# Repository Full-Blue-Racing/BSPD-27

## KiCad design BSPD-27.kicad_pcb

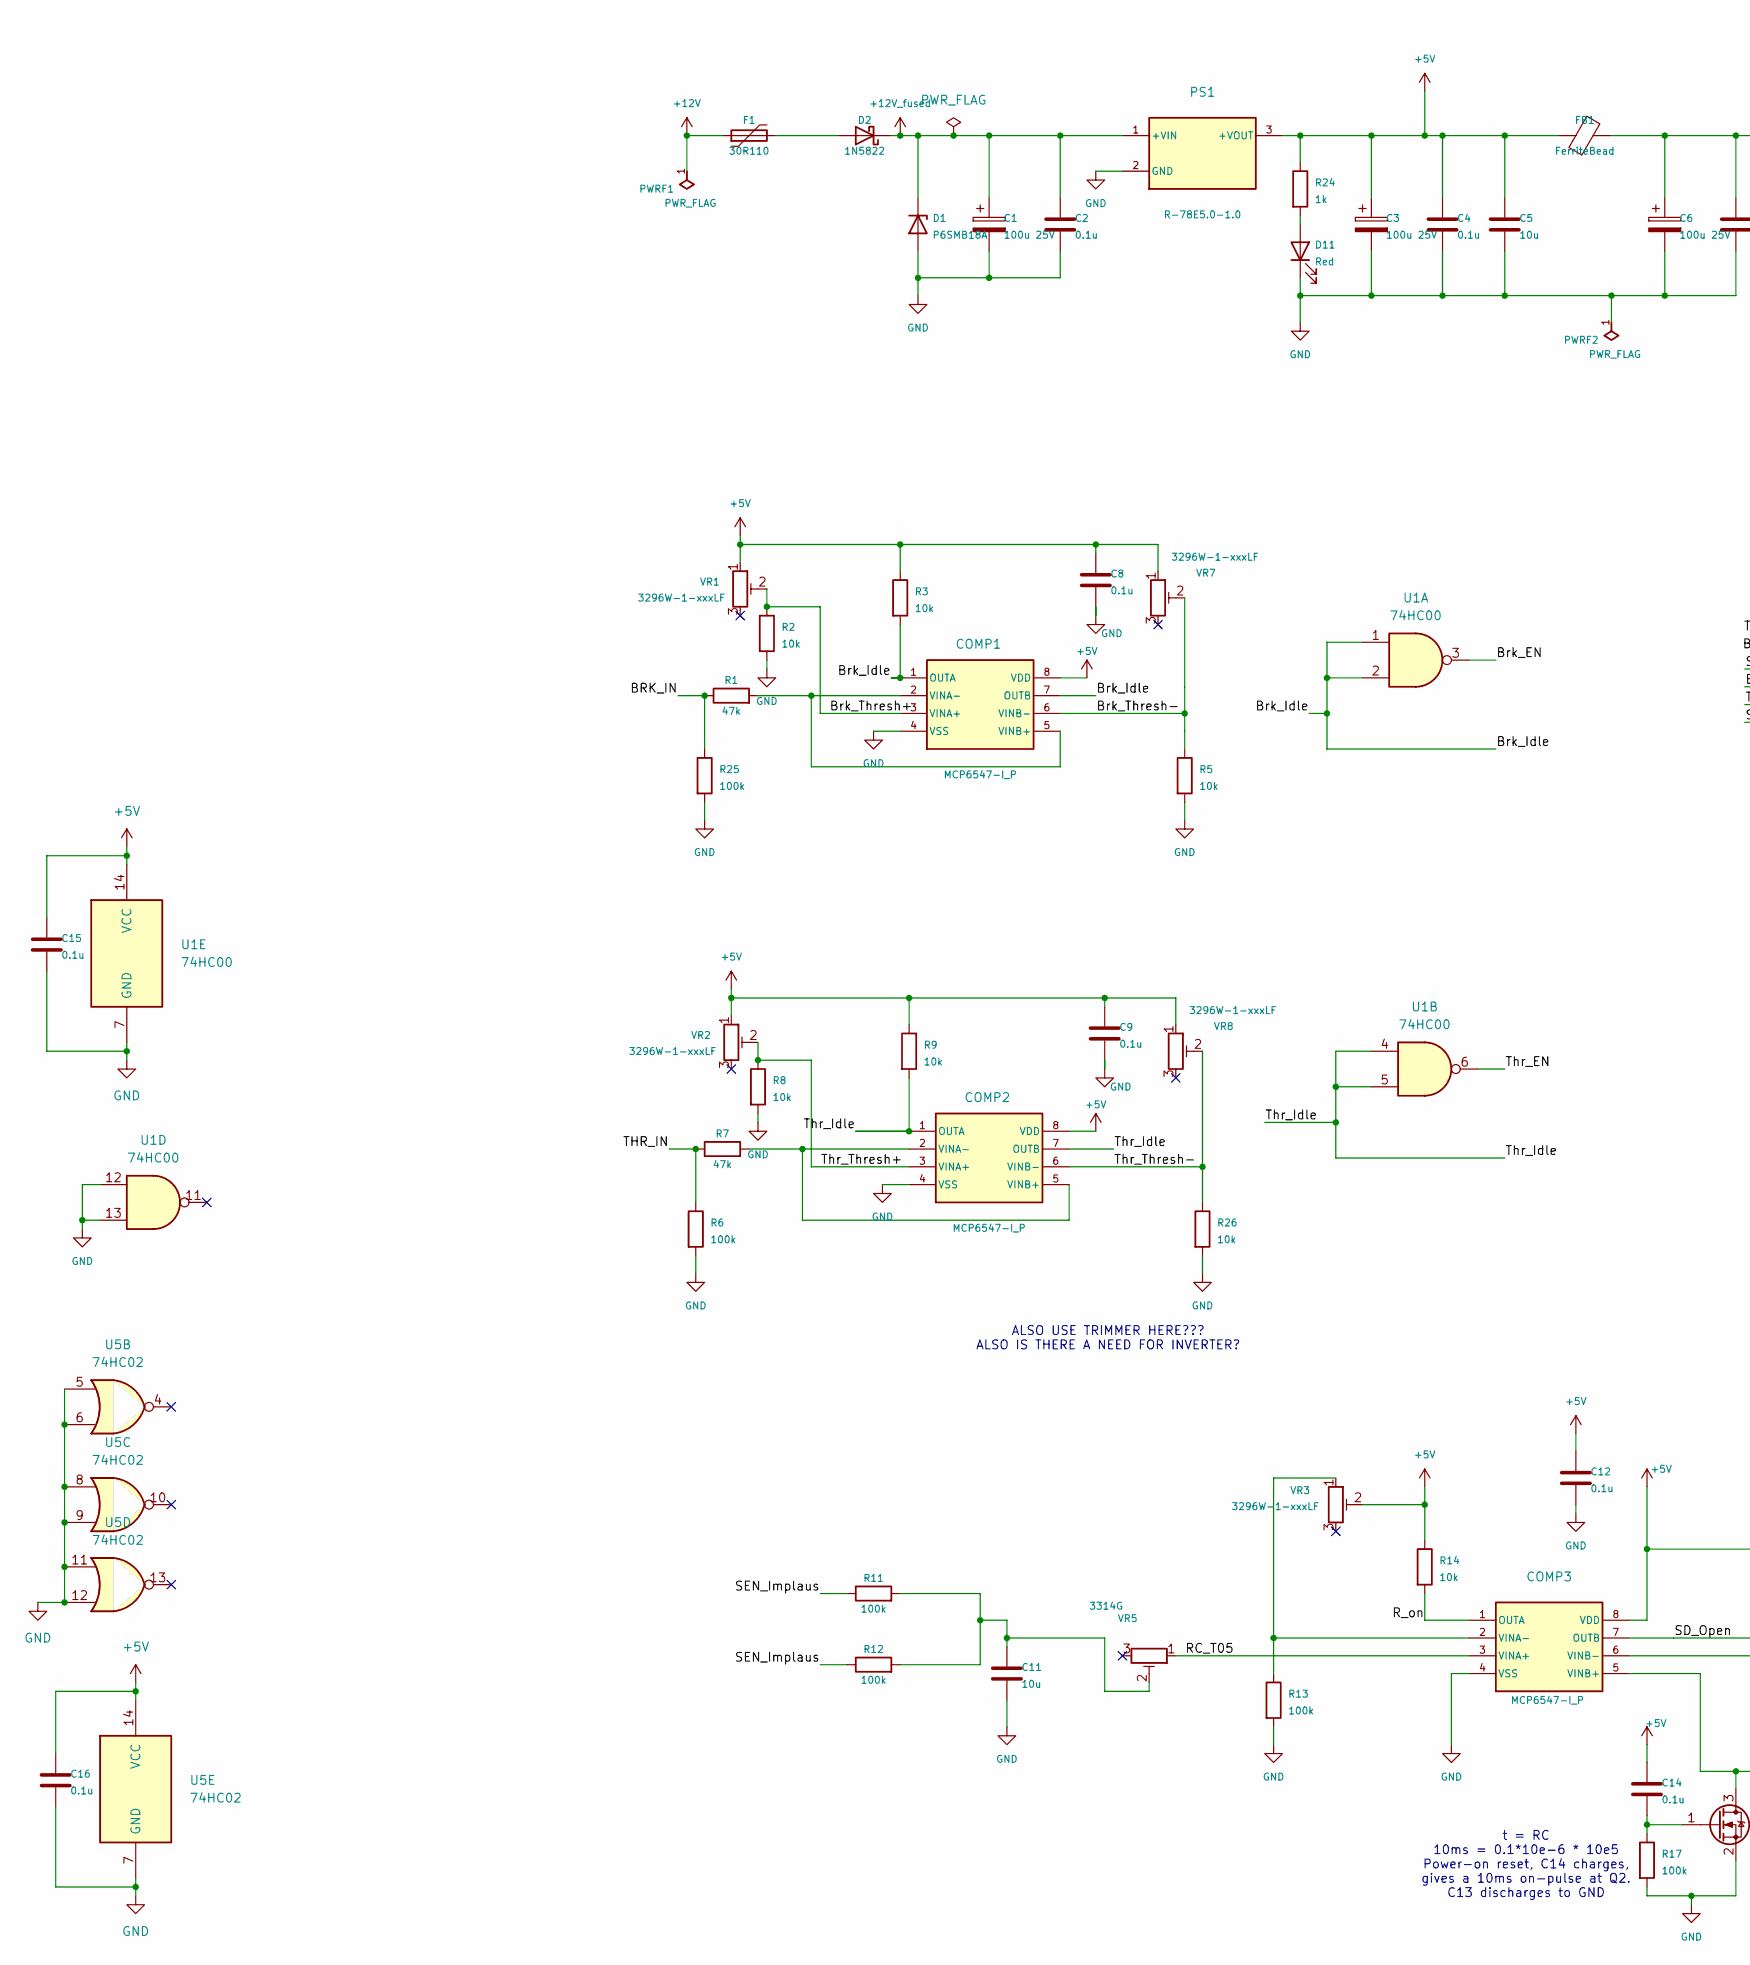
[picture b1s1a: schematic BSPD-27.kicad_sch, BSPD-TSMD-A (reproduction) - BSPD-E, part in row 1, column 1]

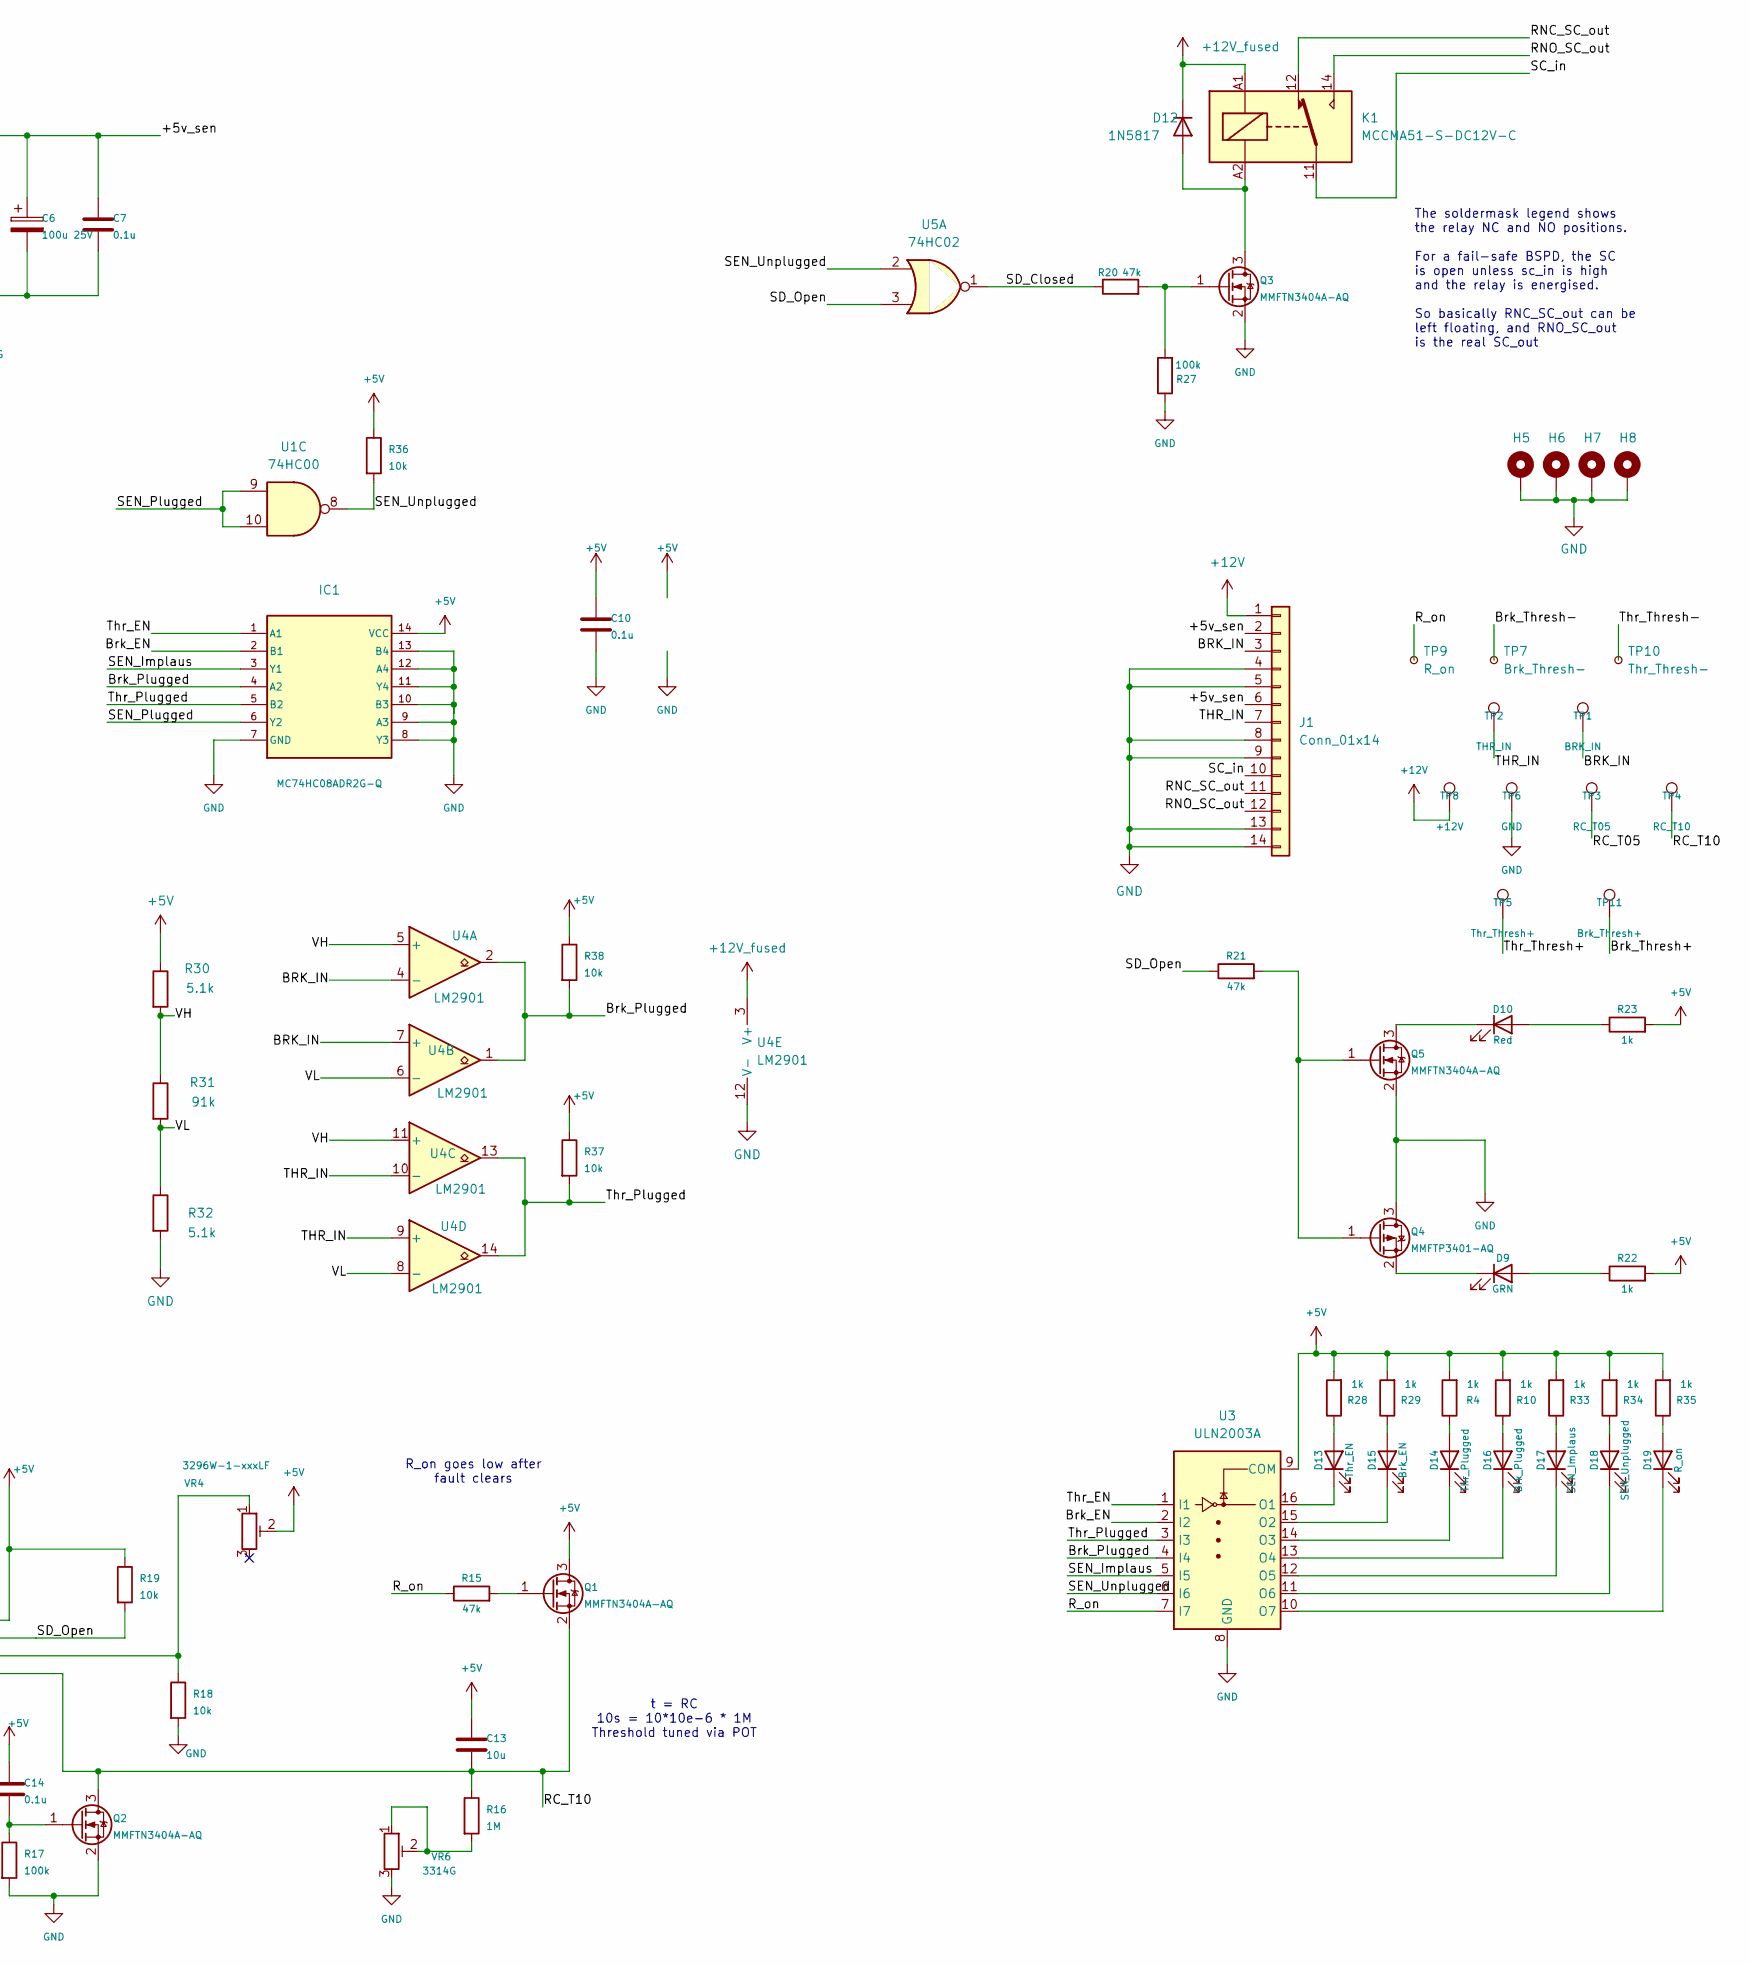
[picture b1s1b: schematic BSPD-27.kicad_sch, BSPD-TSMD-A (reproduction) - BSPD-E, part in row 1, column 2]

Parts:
C1, C3, C6: 100u 25V; CP_Elec_6.3x7.7; MPN RVT1E101M0607; LCSC C72477
C2, C4, C7, C8, C9, C10, C12, C14, C15, C16: 0.1u; C_0805_2012Metric; MPN CC0805KRX7R9BB104; LCSC C49678
C5, C11, C13: 10u; C_0805_2012Metric; MPN CL21A106KAYNNNE; LCSC C15850
COMP1, COMP2, COMP3: MCP6547-I_P; MSOP-8_3x3mm_P0.65mm; MPN MCP6547T-E/MS; Farnell 2851683
D1: P6SMB18A; D_SMB; MPN P6SMB18A; LCSC C80394
D2: 1N5822; D_DO-201AD_P12.70mm_Horizontal; MPN 1N5822; LCSC C52023798
D9: GRN; LED_1206_3216Metric; MPN KP-3216MGC; LCSC C598294
D10, D11: Red; LED_1206_3216Metric; MPN KP-3216SURC; LCSC C598298
D12: 1N5817; D_DO-41_SOD81_P10.16mm_Horizontal; MPN 1N5817; LCSC C315569
D13: Thr_EN; LED_1206_3216Metric; MPN KP-3216SURC; LCSC C598298
D14: Thr_Plugged; LED_1206_3216Metric; MPN KP-3216MGC; LCSC C598294
D15: Brk_EN; LED_1206_3216Metric; MPN KP-3216SURC; LCSC C598298
D16: Brk_Plugged; LED_1206_3216Metric; MPN KP-3216MGC; LCSC C598294
D17: SEN_Implaus; LED_1206_3216Metric; MPN KP-3216SURC; LCSC C598298
D18: SEN_Unplugged; LED_1206_3216Metric; MPN KP-3216SURC; LCSC C598298
D19: R_on; LED_1206_3216Metric; MPN KP-3216SURC; LCSC C598298
F1: 30R110; Fuse_1812_4532Metric; MPN 1812L110/33GR; LCSC C7542972
FB1: FerriteBead; L_1206_3216Metric; MPN CBW321609U102T; LCSC C113327
H5, H6, H7, H8: MountingHole_Pad; MountingHole_3.2mm_M3_Pad_Via
IC1: MC74HC08ADR2G-Q; SOIC-14_3.9x8.7mm_P1.27mm; MPN MC74HC08ADR2G; LCSC C7578
J1: Conn_01x14; TE_776267-1
K1: MCCMA51-S-DC12V-C
PS1: R-78E5.0-1.0; Converter_DCDC_RECOM_R-78E-0.5_THT; MPN R-78E5.0-1.0; Farnell 2760747
PWRF1, PWRF2: PWR_FLAG
Q1, Q2, Q3, Q5: MMFTN3404A-AQ; SOT-23; MPN MMFTN3404A-AQ; Farnell 4680838
Q4: MMFTP3401-AQ; SOT-23; MPN MMFTP3401-AQ; Farnell 4855254
R1, R7, R15, R20, R21: 47k; R_0805_2012Metric; MPN 0805W8F4702T5E; LCSC C17713
R2, R3, R5, R8, R9, R14, R18, R19, R26, R36, R37, R38: 10k; R_0805_2012Metric; MPN 0805W8F1002T5E; LCSC C17414
R4, R10, R22, R23, R24, R28, R29, R33, R34, R35: 1k; R_1206_3216Metric; MPN 1206W4F1001T5E; LCSC C4410
R6, R11, R12, R13, R17, R25, R27: 100k; R_1206_3216Metric; MPN ERA-8AEB104V; LCSC C2073484
R16: 1M; R_1206_3216Metric; MPN RT1206DRE071ML; LCSC C872103
R30, R32: 5.1k; R_1206_3216Metric; MPN FRC1206F5101TS; LCSC C2933721
R31: 91k; R_1206_3216Metric; MPN FRC1206J913TS; LCSC C2933797
TP1: BRK_IN; TestPoint_Loop_D2.54mm_Drill1.5mm_Beaded
TP2: THR_IN; TestPoint_Loop_D2.54mm_Drill1.5mm_Beaded
TP3: RC_T05; TestPoint_Loop_D2.54mm_Drill1.5mm_Beaded
TP4: RC_T10; TestPoint_Loop_D2.54mm_Drill1.5mm_Beaded
TP5: Thr_Thresh+; TestPoint_Loop_D2.54mm_Drill1.5mm_Beaded
TP6: GND; TestPoint_Loop_D2.54mm_Drill1.5mm_Beaded
TP7: Brk_Thresh-; TestPoint_Pad_D2.0mm
TP8: +12V; TestPoint_Loop_D2.54mm_Drill1.5mm_Beaded
TP9: R_on; TestPoint_Pad_D2.0mm
TP10: Thr_Thresh-; TestPoint_Pad_D2.0mm
TP11: Brk_Thresh+; TestPoint_Loop_D2.54mm_Drill1.5mm_Beaded
U1: 74HC00; SOIC-14_3.9x8.7mm_P1.27mm; MPN SN74HC00DR; LCSC C10090
U3: ULN2003A; SOIC-16_3.9x9.9mm_P1.27mm; MPN ULN2003ADR; LCSC C7512
U4: LM2901; SOIC-14_3.9x8.7mm_P1.27mm; MPN LM2901DR; LCSC C7932
U5: 74HC02; SOIC-14_3.9x8.7mm_P1.27mm; MPN SN74HC02DR; LCSC C350559
VR1, VR2, VR3, VR4, VR7, VR8: 3296W-1-xxxLF; Potentiometer_Bourns_3296W_Vertical; MPN 3296W-1-104LF; LCSC C48084
VR5, VR6: 3314G; Potentiometer_Bourns_3314G_Vertical; MPN 3314G-1-104E; LCSC C780219

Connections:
+5V: C3.1, C4.1, C5.1, C8.1, C9.1, C10.1, C12.1, C13.1, C14.1, C15.1, C16.1, COMP1.8 (VDD), COMP2.8 (VDD), COMP3.8 (VDD), FB1.1, IC1.14 (VCC), PS1.3 (+VOUT), Q1.3 (D), R3.1, R4.2, R9.1, R10.2, R14.1, R19.1, R22.2, R23.2, R24.1, R28.2, R29.2, R30.1, R33.2, R34.2, R35.2, R36.1, R37.1, R38.1, U1.14 (VCC), U3.9 (COM), U5.14 (VCC), VR1.1, VR2.1, VR3.2, VR4.2, VR7.1, VR8.1
+12V: F1.1, J1.1, PWRF1.1, TP8.1
+12V_fused: C1.1, C2.1, D1.1 (K), D2.1 (K), D12.1 (K), K1.A1, PS1.1 (+VIN), U4.3 (V+)
/+5v_sen: C6.1, C7.1, FB1.2, J1.2, J1.6
/BRK_IN: J1.3, R1.1, R25.1, TP1.1, U4.4 (-), U4.7 (+)
/Brk_EN: IC1.2 (B1), U1.3, U3.2 (I2)
/Brk_Idle: COMP1.1 (OUTA), COMP1.7 (OUTB), R3.2, U1.1, U1.2
/Brk_Plugged: IC1.4 (A2), R38.2, U3.4 (I4), U4.1, U4.2
/Brk_Thresh+: COMP1.3 (VINA+), R2.1, TP11.1, VR1.2
/Brk_Thresh-: COMP1.6 (VINB-), R5.1, TP7.1, VR7.2
/RC_T05: COMP3.3 (VINA+), TP3.1, VR5.1
/RC_T10: C13.2, COMP3.5 (VINB+), Q1.2 (S), Q2.3 (D), R16.1, TP4.1
/RNC_SC_out: J1.11, K1.12
/RNO_SC_out: J1.12, K1.14
/R_on: COMP3.1 (OUTA), R14.2, R15.1, TP9.1, U3.7 (I7)
/SC_in: J1.10, K1.11
/SD_Closed: R20.1, U5.1
/SD_Open: COMP3.7 (OUTB), R19.2, R21.1, U5.3
/SEN_Implaus: IC1.3 (Y1), R11.1, R12.1, U3.5 (I5)
/SEN_Plugged: IC1.6 (Y2), U1.9, U1.10
/SEN_Unplugged: R36.2, U1.8, U3.6 (I6), U5.2
/THR_IN: J1.7, R6.1, R7.1, TP2.1, U4.9 (+), U4.10 (-)
/Thr_EN: IC1.1 (A1), U1.6, U3.1 (I1)
/Thr_Idle: COMP2.1 (OUTA), COMP2.7 (OUTB), R9.2, U1.4, U1.5
/Thr_Plugged: IC1.5 (B2), R37.2, U3.3 (I3), U4.13, U4.14
/Thr_Thresh+: COMP2.3 (VINA+), R8.1, TP5.1, VR2.2
/Thr_Thresh-: COMP2.6 (VINB-), R26.1, TP10.1, VR8.2
/VH: R30.2, R31.1, U4.5 (+), U4.11 (+)
/VL: R31.2, R32.1, U4.6 (-), U4.8 (-)
GND: C1.2, C2.2, C3.2, C4.2, C5.2, C6.2, C7.2, C8.2, C9.2, C10.2, C11.2, C12.2, C15.2, C16.2, COMP1.4 (VSS), COMP2.4 (VSS), COMP3.4 (VSS), D1.2 (A), D11.1 (K), H5.1, H6.1, H7.1, H8.1, IC1.7 (GND), IC1.8 (Y3), IC1.9 (A3), IC1.10 (B3), IC1.11 (Y4), IC1.12 (A4), IC1.13 (B4), J1.4, J1.5, J1.8, J1.9, J1.13, J1.14, PS1.2 (GND), PWRF2.1, Q2.2 (S), Q3.2 (S), Q4.3 (D), Q5.2 (S), R2.2, R5.2, R6.2, R8.2, R13.2, R17.2, R18.2, R25.2, R26.2, R27.1, R32.2, TP6.1, U1.7 (GND), U1.12, U1.13, U3.8 (GND), U4.12 (V-), U5.5, U5.6, U5.7 (GND), U5.8, U5.9, U5.11, U5.12, VR6.3
unnamed: C11.1, R11.2, R12.2, VR5.2
unnamed: COMP1.2 (VINA-), COMP1.5 (VINB+), R1.2
unnamed: COMP2.2 (VINA-), COMP2.5 (VINB+), R7.2
unnamed: COMP3.2 (VINA-), R13.1, VR3.1
unnamed: COMP3.6 (VINB-), R18.1, VR4.1
unnamed: D2.2 (A), F1.2
unnamed: D9.2 (A), R22.1
unnamed: D9.1 (K), Q4.2 (S)
unnamed: D10.2 (A), R23.1
unnamed: D10.1 (K), Q5.3 (D)
unnamed: D11.2 (A), R24.2
unnamed: D12.2 (A), K1.A2, Q3.3 (D)
unnamed: D13.2 (A), R28.1
unnamed: D13.1 (K), U3.16 (O1)
unnamed: D14.2 (A), R4.1
unnamed: D14.1 (K), U3.14 (O3)
unnamed: D15.2 (A), R29.1
unnamed: D15.1 (K), U3.15 (O2)
unnamed: D16.2 (A), R10.1
unnamed: D16.1 (K), U3.13 (O4)
unnamed: D17.2 (A), R33.1
unnamed: D17.1 (K), U3.12 (O5)
unnamed: D18.2 (A), R34.1
unnamed: D18.1 (K), U3.11 (O6)
unnamed: D19.2 (A), R35.1
unnamed: D19.1 (K), U3.10 (O7)
unnamed: Q1.1 (G), R15.2
unnamed: C14.2, Q2.1 (G), R17.1
unnamed: Q3.1 (G), R20.2, R27.2
unnamed: Q4.1 (G), Q5.1 (G), R21.2
unnamed: R16.2, VR6.1, VR6.2

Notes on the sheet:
The soldermask legend shows the relay NC and NO positions. For a fail-safe BSPD, the SC is open unless sc_in is high and the relay is energised. So basically RNC_SC_out can be left floating, and RNO_SC_out is the real SC_out
R_on goes low after fault clears
ALSO USE TRIMMER HERE??? ALSO IS THERE A NEED FOR INVERTER?
t = RC 10ms = 0.1*10e-6 * 10e5 Power-on reset, C14 charges, gives a 10ms on-pulse at Q2. C13 discharges to GND
t = RC 10s = 10*10e-6 * 1M Threshold tuned via POT

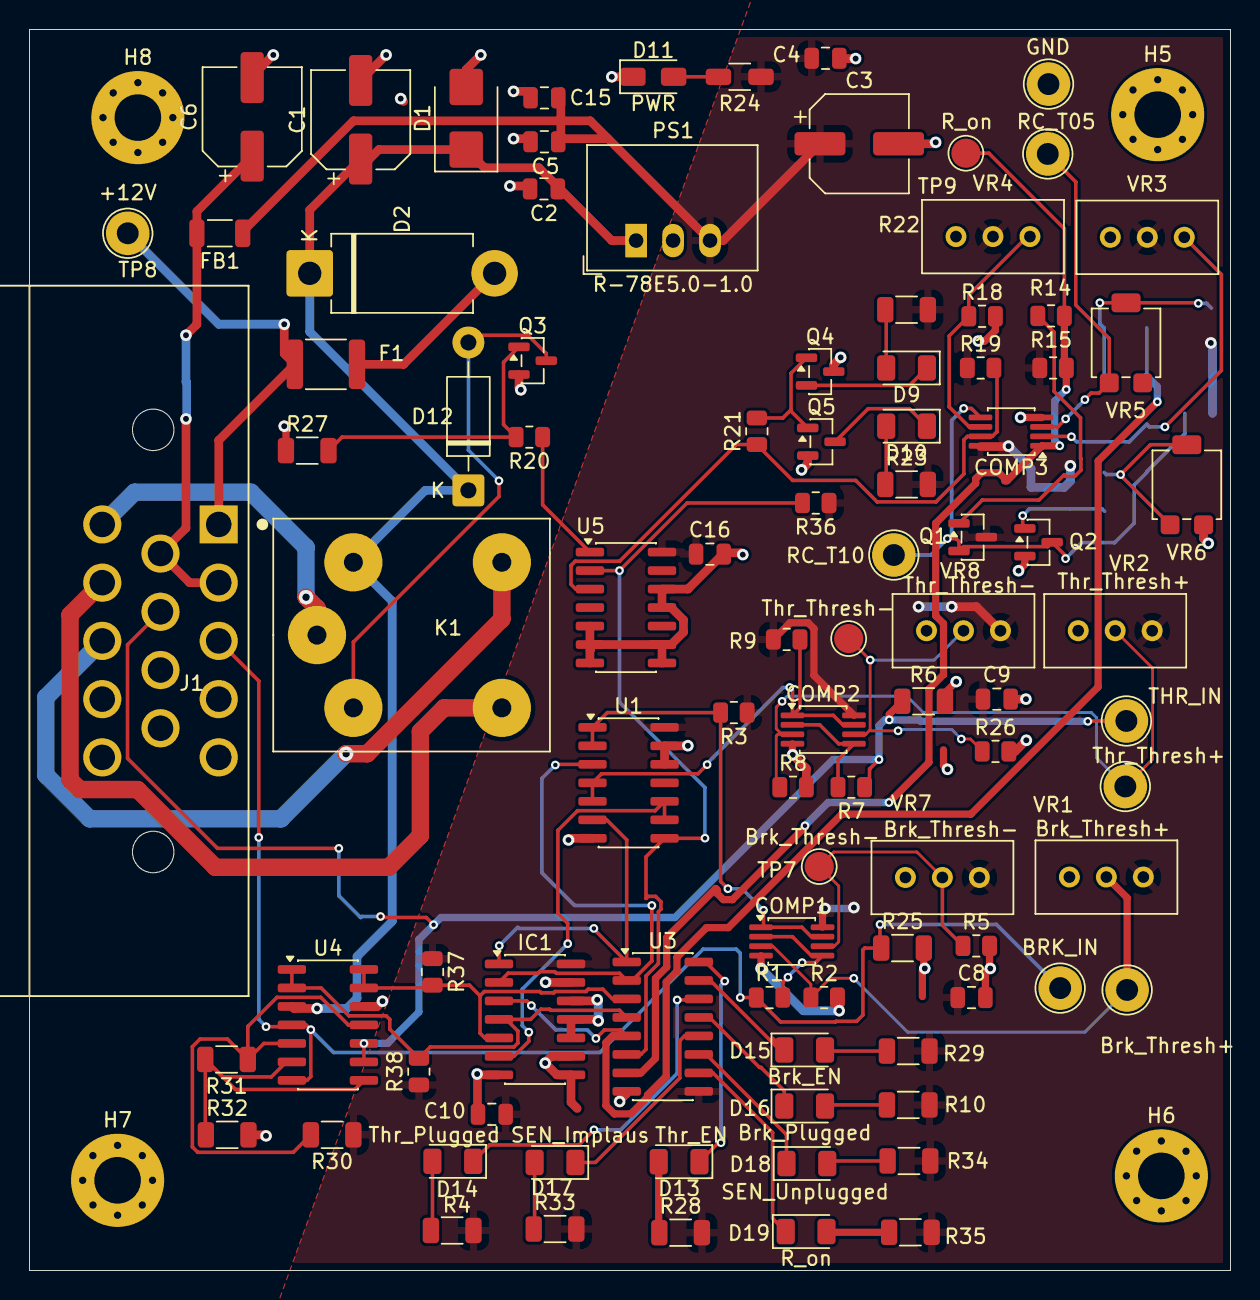
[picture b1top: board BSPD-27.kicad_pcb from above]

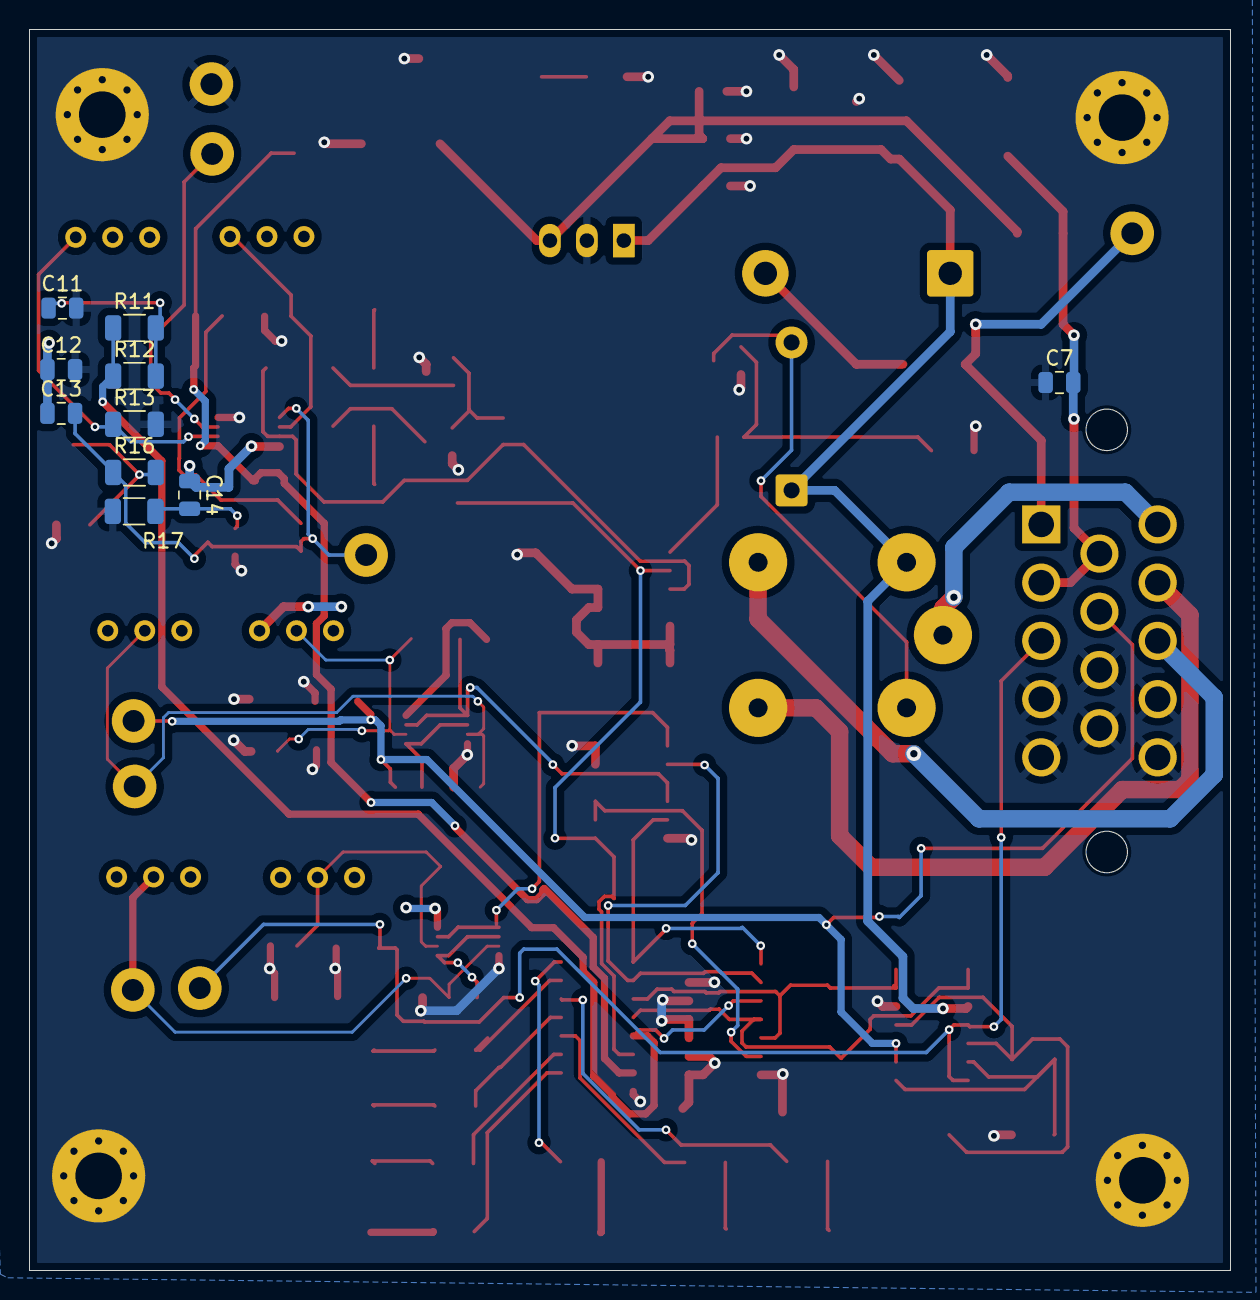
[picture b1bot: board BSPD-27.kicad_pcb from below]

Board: 2 copper layers, 82.5 x 85.2 mm, 108 parts (10 on the bottom side), 61 nets.

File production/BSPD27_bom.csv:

Designator,Footprint,Quantity,Value,LCSC Part #
"C1, C3, C6",CP_Elec_6.3x7.7,3,100u 25V,C72477
"C10, C12, C14, C15, C16, C2, C4, C7, C8, C9",0805,10,0.1u,C49678
"C11, C13, C5",0805,3,10u,C15850
"COMP1, COMP2, COMP3",MSOP-8_3x3mm_P0.65mm,3,MCP6547-I_P,MCP6547T-E/MS
D1,D_SMB,1,P6SMB18A,C80394
D10,1206,1,Red,C598298
D11,1206,1,PWR,C598298
D12,D_DO-41_SOD81_P10.16mm_Horizontal,1,1N5817,C315569
D13,1206,1,Thr_EN,C598298
D14,1206,1,Thr_Plugged,C598294
D15,1206,1,Brk_EN,C598298
D16,1206,1,Brk_Plugged,C598294
D17,1206,1,SEN_Implaus,C598298
D18,1206,1,SEN_Unplugged,C598298
D19,1206,1,R_on,C598298
D2,D_DO-201AD_P12.70mm_Horizontal,1,1N5822,C52023798
D9,1206,1,GRN,C598294
F1,1812,1,30R110,C7542972
FB1,1206,1,FerriteBead,C113327
IC1,SOIC-14_3.9x8.7mm_P1.27mm,1,MC74HC08ADR2G-Q,C7578
J1,TE_776267-1,1,Conn_01x14,
K1,MCCMA51-S-DC12V-C,1,MCCMA51-S-DC12V-C,
PS1,Converter_DCDC_RECOM_R-78E-0.5_THT,1,R-78E5.0-1.0,R-78E5.0-1.0
"Q1, Q2, Q3, Q5",SOT-23,4,MMFTN3404A-AQ,MMFTN3404A-AQ
Q4,SOT-23,1,MMFTP3401-AQ,MMFTP3401-AQ
"R1, R15, R20, R21, R7",0805,5,47k,C17713
"R10, R22, R23, R24, R28, R29, R33, R34, R35, R4",1206,10,1k,C4410
"R11, R12, R13, R17, R25, R27, R6",1206,7,100k,C2073484
"R14, R18, R19, R2, R26, R3, R36, R37, R38, R5, R8, R9",0805,12,10k,C17414
R16,1206,1,1M,C872103
"R30, R32",1206,2,5.1k,C2933721
R31,1206,1,91k,C2933797
TP1,TestPoint_Loop_D2.54mm_Drill1.5mm_Beaded,1,BRK_IN,
TP10,TestPoint_Pad_D2.0mm,1,Thr_Thresh-,
TP11,TestPoint_Loop_D2.54mm_Drill1.5mm_Beaded,1,Brk_Thresh+,
TP2,TestPoint_Loop_D2.54mm_Drill1.5mm_Beaded,1,THR_IN,
TP3,TestPoint_Loop_D2.54mm_Drill1.5mm_Beaded,1,RC_T05,
TP4,TestPoint_Loop_D2.54mm_Drill1.5mm_Beaded,1,RC_T10,
TP5,TestPoint_Loop_D2.54mm_Drill1.5mm_Beaded,1,Thr_Thresh+,
TP6,TestPoint_Loop_D2.54mm_Drill1.5mm_Beaded,1,GND,
TP7,TestPoint_Pad_D2.0mm,1,Brk_Thresh-,
TP8,TestPoint_Loop_D2.54mm_Drill1.5mm_Beaded,1,+12V,
TP9,TestPoint_Pad_D2.0mm,1,R_on,
U1,SOIC-14_3.9x8.7mm_P1.27mm,1,74HC00,C10090
U3,SOIC-16_3.9x9.9mm_P1.27mm,1,ULN2003A,C7512
U4,SOIC-14_3.9x8.7mm_P1.27mm,1,LM2901,C7932
U5,SOIC-14_3.9x8.7mm_P1.27mm,1,74HC02,C350559
VR1,Potentiometer_Bourns_3296W_Vertical,1,Brk_Thresh+,C48084
VR2,Potentiometer_Bourns_3296W_Vertical,1,Thr_Thresh+,C48084
"VR3, VR4",Potentiometer_Bourns_3296W_Vertical,2,3296W-1-xxxLF,C48084
"VR5, VR6",Potentiometer_Bourns_3314G_Vertical,2,3314G,C780219
VR7,Potentiometer_Bourns_3296W_Vertical,1,Brk_Thresh-,C48084
VR8,Potentiometer_Bourns_3296W_Vertical,1,Thr_Thresh-,C48084
